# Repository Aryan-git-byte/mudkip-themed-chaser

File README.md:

# Mudkip Themed LED Chaser using NE555

this is a cool mudkip themed led chaser built using a ne555 timer and cd4017 decade counter. the 555 is configured in astable mode to generate clock pulses, and the 4017 drives 10 leds one by one to create a smooth chasing effect.

the pcb outline is shaped like mudkip, and the leds are arranged along the body to make the animation flow across the board.

---

## how it works

- the ne555 is set in astable mode to generate continuous clock pulses  
- the cd4017 receives those pulses and activates outputs q0 to q9 sequentially  
- each output drives one led  
- only one led is on at a time, creating the chasing effect  

the board runs on 5v and uses through hole components for easy soldering.

---

## schematic

---

## 3d view

---

## pcb details

- 2 layer pcb  
- custom mudkip shaped outline  
- ground plane on bottom layer  
- 1oz copper  
- 1.6mm thickness  

---

## what i learned

- configuring the 555 in astable mode  
- using the cd4017 decade counter  
- designing a custom shaped pcb  
- routing a tight board layout  
- generating gerbers and preparing for manufacturing  

---

this project combines basic electronics with creative pcb design and fabrication.

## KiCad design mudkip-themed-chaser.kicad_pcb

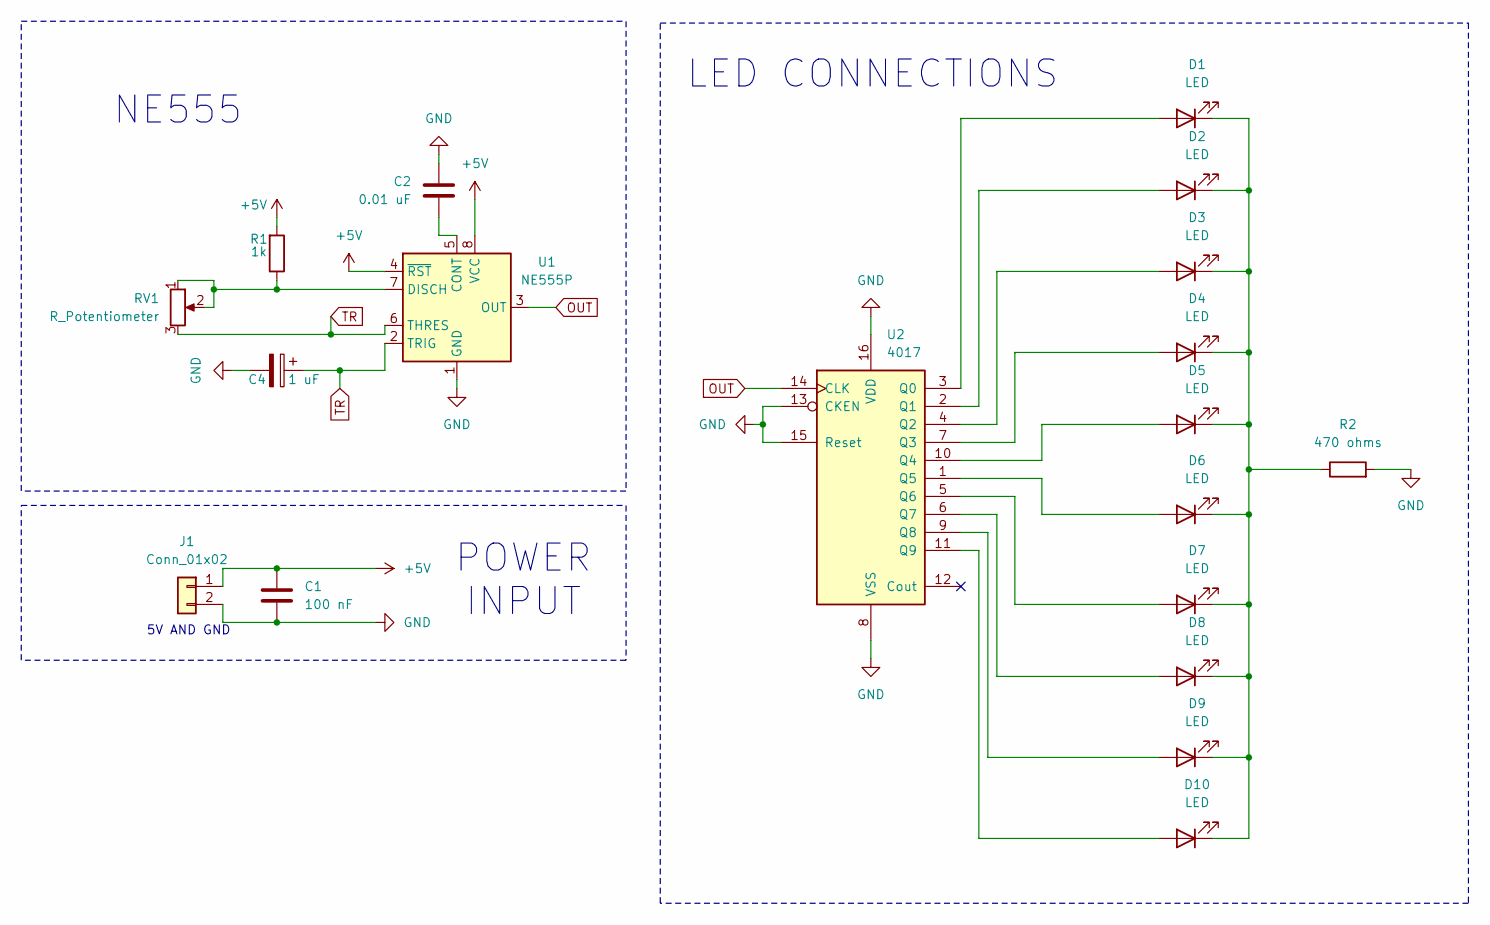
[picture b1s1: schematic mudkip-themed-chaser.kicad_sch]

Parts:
C1: 100 nF; C_Disc_D7.5mm_W2.5mm_P5.00mm
C2: 0.01 uF; C_Disc_D7.5mm_W2.5mm_P5.00mm
C4: 1 uF; CP_Radial_D5.0mm_P2.00mm
D1, D2, D3, D4, D5, D6, D7, D8, D9, D10: LED; LED_D3.0mm
J1: Conn_01x02; PinHeader_1x02_P2.54mm_Vertical
R1: 1k; R_Axial_DIN0207_L6.3mm_D2.5mm_P7.62mm_Horizontal
R2: 470 ohms; R_Axial_DIN0207_L6.3mm_D2.5mm_P7.62mm_Horizontal
RV1: R_Potentiometer; Potentiometer_Vishay_T93YA_Vertical
U1: NE555P; DIP-8_W7.62mm
U2: 4017; N16

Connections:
+5V: C1.1, J1.1, R1.2, U1.4 (~RST), U1.8 (VCC)
GND: C1.2, C2.1, C4.2, J1.2, R2.2, U1.1 (GND), U2.8 (VSS), U2.13 (CKEN), U2.15 (Reset), U2.16 (VDD)
unnamed: D1.2 (A), U2.3 (Q0)
unnamed: D1.1 (K), D2.1 (K), D3.1 (K), D4.1 (K), D5.1 (K), D6.1 (K), D7.1 (K), D8.1 (K), D9.1 (K), D10.1 (K), R2.1
unnamed: D2.2 (A), U2.2 (Q1)
unnamed: D3.2 (A), U2.4 (Q2)
unnamed: D4.2 (A), U2.7 (Q3)
unnamed: D5.2 (A), U2.10 (Q4)
unnamed: D6.2 (A), U2.1 (Q5)
unnamed: D7.2 (A), U2.5 (Q6)
unnamed: D8.2 (A), U2.6 (Q7)
unnamed: D9.2 (A), U2.9 (Q8)
unnamed: D10.2 (A), U2.11 (Q9)
unnamed: C2.2, U1.5 (CONT)
unnamed: R1.1, RV1.1, RV1.2, U1.7 (DISCH)
OUT: U1.3 (OUT), U2.14 (CLK)
TR: C4.1, RV1.3, U1.2 (TRIG), U1.6 (THRES)

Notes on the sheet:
NE555
LED CONNECTIONS
5V AND GND
POWER INPUT

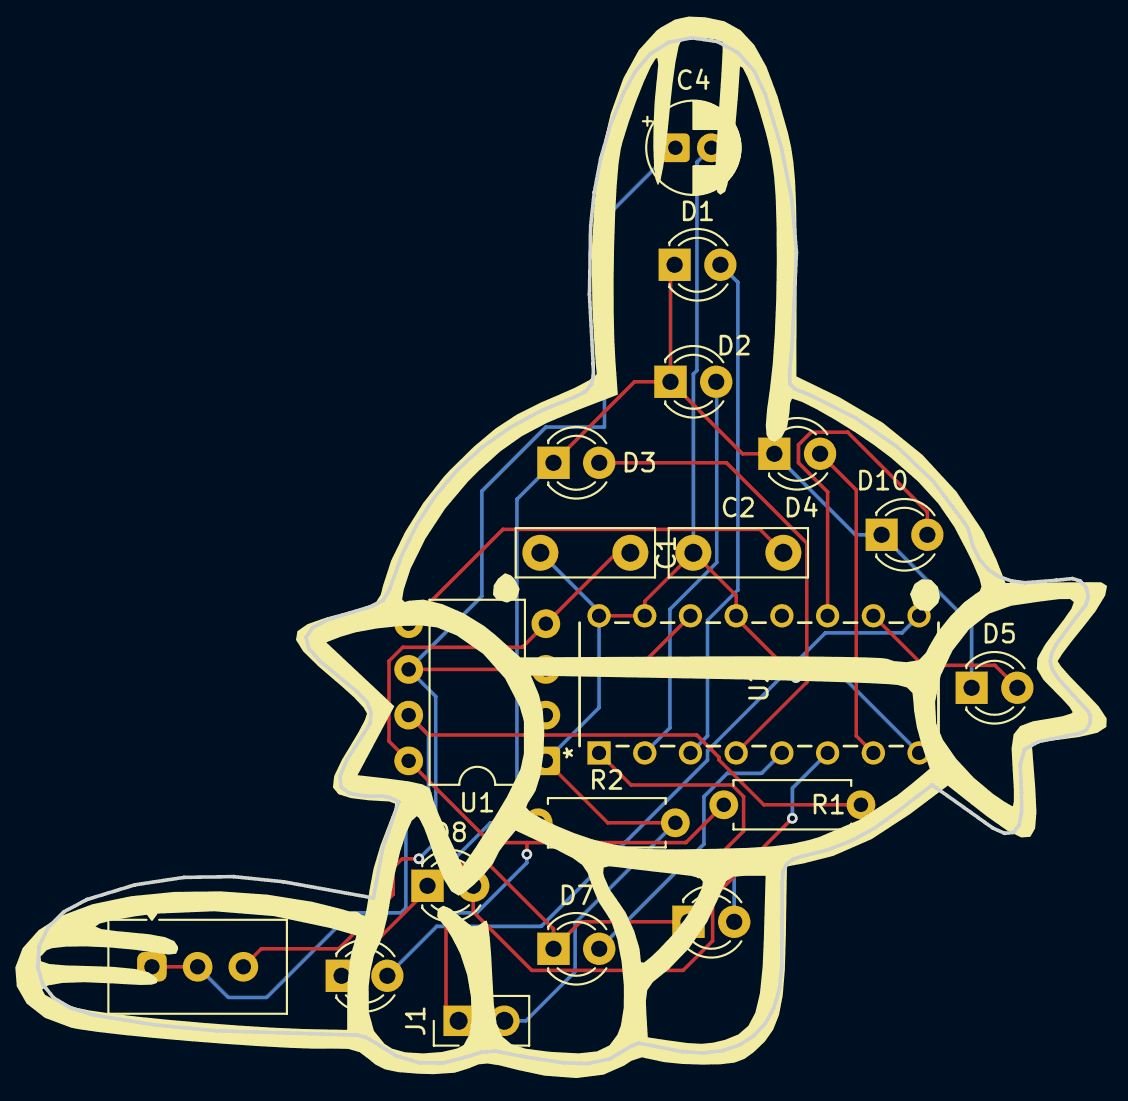
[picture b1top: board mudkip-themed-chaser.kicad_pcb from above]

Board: 2 copper layers, 58.5 x 57.0 mm, 19 parts (0 on the bottom side), 17 nets.

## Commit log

2026-02-16 added image.png
2026-02-16 added readme.md
2026-02-16 adeed schematic pdf
2026-02-18 added silkscreens
2026-02-18 up-to-date
